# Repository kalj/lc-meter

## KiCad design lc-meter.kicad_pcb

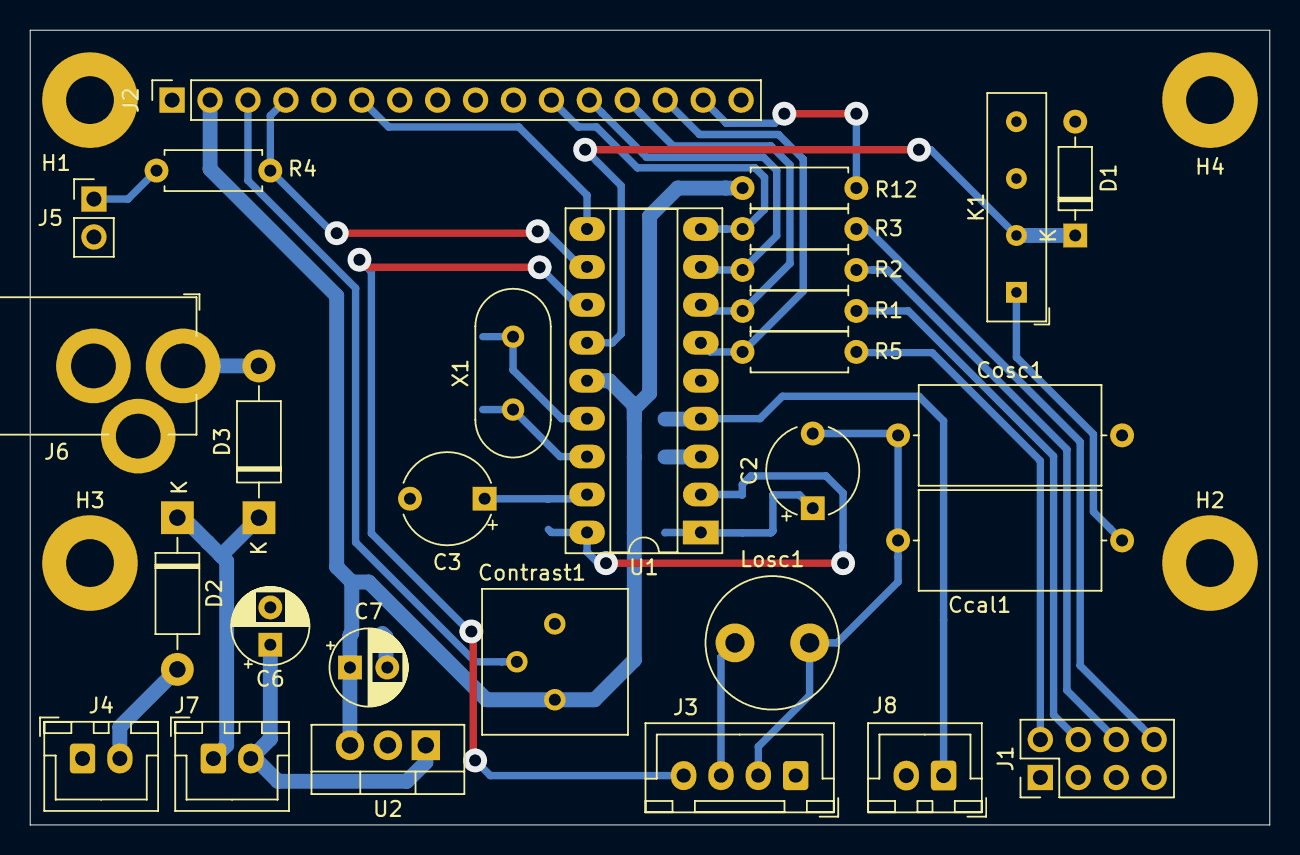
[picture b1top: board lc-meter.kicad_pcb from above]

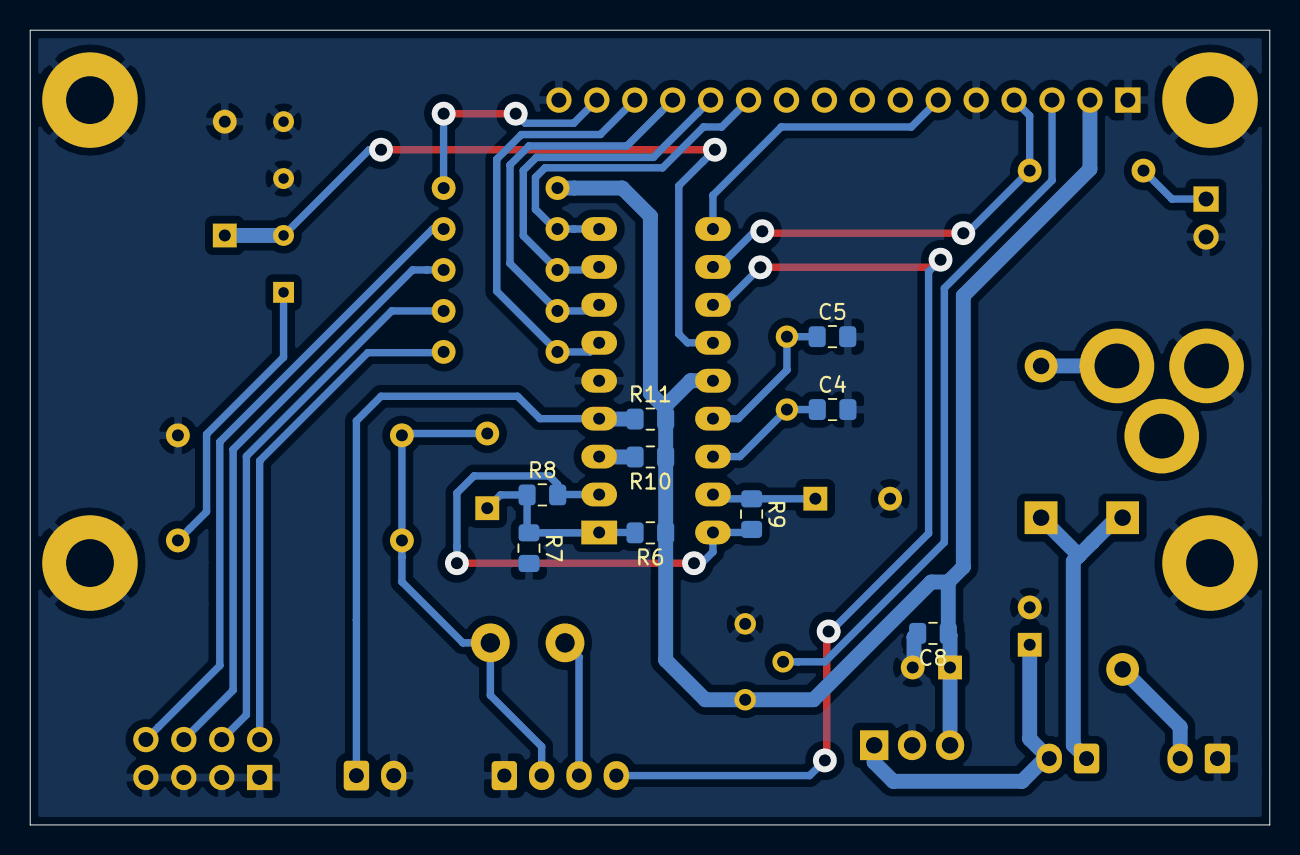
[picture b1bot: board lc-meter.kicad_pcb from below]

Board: 2 copper layers, 83.0 x 53.2 mm, 42 parts (9 on the bottom side), 31 nets.

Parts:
C2, C3: 10µF; CP_Radial_Tantal_D6.0mm_P5.00mm
C4, C5: 33pF; C_0805_2012Metric_Pad1.15x1.40mm_HandSolder
C6: 22µF; CP_Radial_D5.0mm_P2.50mm
C7: 10µF; CP_Radial_D5.0mm_P2.50mm
C8: 100nF; C_0805_2012Metric_Pad1.15x1.40mm_HandSolder
Ccal1: 1000pF; C_Axial_L12.0mm_D6.5mm_P15.00mm_Horizontal
Contrast1: 10k; Potentiometer_Bourns_3386P_Vertical
Cosc1: 1000pF; C_Axial_L12.0mm_D6.5mm_P15.00mm_Horizontal
D1: 1N914; D_DO-35_SOD27_P7.62mm_Horizontal
D2, D3: 1N4004; D_DO-41_SOD81_P10.16mm_Horizontal
H1, H2, H3, H4: MountingHole_Pad; MountingHole_3.2mm_M3_Pad
J1: Jumpers; PinHeader_2x04_P2.54mm_Vertical
J2: LCD; PinSocket_1x16_P2.54mm_Vertical
J3: Input Switch; JST_XH_B4B-XH-A_1x04_P2.50mm_Vertical
J4: 9V Battery; JST_XH_B2B-XH-A_1x02_P2.50mm_Vertical
J5: LcdMode; PinHeader_1x02_P2.54mm_Vertical
J6: Barrel_Jack_Switch; BarrelJack_Horizontal_CircularHoles
J7: PowerSwitch; JST_XH_B2B-XH-A_1x02_P2.50mm_Vertical
J8: ResetSwitch; JST_XH_B2B-XH-A_1x02_P2.50mm_Vertical
K1: MSxx-1Axx-75; Relay_SPST_StandexMeder_MS_Form1AB
Losc1: 100µH; L_Radial_D8.7mm_P5.00mm_Fastron_07HCP
R1, R2, R3, R4, R5: 1k; R_Axial_DIN0207_L6.3mm_D2.5mm_P7.62mm_Horizontal
R6, R7, R8: 100k; R_0805_2012Metric_Pad1.15x1.40mm_HandSolder
R9: 47k; R_0805_2012Metric_Pad1.15x1.40mm_HandSolder
R10, R11: 4k7; R_0805_2012Metric_Pad1.15x1.40mm_HandSolder
R12: 500; R_Axial_DIN0207_L6.3mm_D2.5mm_P7.62mm_Horizontal
U1: PIC16F628-xxIP; DIP-18_W7.62mm_Socket_LongPads
U2: L7805; TO-220-3_Vertical
X1: Crystal; Crystal_HC49-U_Vertical

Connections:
/CheckF1: J1.6, R2.1
/CheckF2: J1.8, R3.1
/CmpNet1: R8.2, R9.2, U1.2, U1.18
/CmpNet2: C2.1, R6.2, R7.1, R8.1, U1.1
/CmpNet3: C3.1, R9.1, U1.17
/LcdDB4: J2.11, R3.2, U1.9
/LcdDB5: J2.12, R2.2, U1.8
/LcdDB6: J2.13, R1.2, U1.7
/LcdDB7: J2.14, R5.2, U1.6
/LcdE: J2.6, U1.10
/LcdMode: J5.1, R4.1
/LcdRS: J2.4, R4.2, U1.11
/LcdVo: Contrast1.2, J2.3
/LowerCcal: J1.4, R1.1
/RaiseCcal: J1.2, R5.1
/Relay: D1.1, K1.3, U1.13
/Vcc: C7.1, C8.1, Contrast1.3, J2.2, R6.1, R10.1, R11.2, R12.1, U1.14, U2.3
/Vin: C6.1, J7.2, U2.1
/Vin9V: D2.2, J4.2
/VinJack: D3.2, J6.1
/VinPreSwitch: D2.1, D3.1, J7.1
/~Lsense: J3.4, U1.12
/~Reset: J8.1, R11.1, U1.4
GNDREF: C3.2, C4.2, C5.2, C6.2, C7.2, C8.2, Contrast1.1, Cosc1.2, D1.2, H1.1, H2.1, H3.1, H4.1, J1.1, J1.3, J1.5, J1.7, J2.1, J2.5, J2.16, J3.1, J4.1, J5.2, J6.2, J8.2, K1.5, K1.7, R7.2, U1.5, U2.2
unnamed: C2.2, Ccal1.1, Cosc1.1, J3.2, Losc1.2
unnamed: C4.1, U1.16, X1.1
unnamed: C5.1, U1.15, X1.2
unnamed: Ccal1.2, K1.1
unnamed: J2.15, R12.2
unnamed: J3.3, Losc1.1
unnamed: R10.2, U1.3

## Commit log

2020-08-21 initial import
